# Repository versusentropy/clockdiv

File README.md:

# eurorack clockdivider

## v0.3 this version is not yet tested!

## Classic CD4024 7 step binary clock-divider

  * 6hp
  * +/-12V 20mA/-
  * 1 PCB 2 layer
    * 73 parts total
    * 14 SMT, 4 THT
  * +5V gate outputs
  * clock input
    * TN pin header on pcb
  * reset input
    * 2nd pin header on pcb

Schematic and layout with KiCad 5. Panel with Inkscape + shenzen2svg → Kicad

Ordered mine at JLCPCB. Gerbers include marking for order number. BOM with part numbers for their assembly service.

Be carful with the transisors' pin numbers, because the 2N3904 schematic symbol doesn't match the MMBT3904 part (, which has its own schematic symbol). 

The CLK input is buffered and inverted by Q2.

The RESET input (and the additional pin-header) are buffered by Q3 & Q4. Q1 resets the clockdivider at startup, until C1 is charged up.

A MMBT3904 buffers each output and its LED. The jack is protected by a diode and a 1k resistor. So multiple jacks can be combined.

On the back pin headers allow connections to other modules (not prtected by diodes, but a 1k resistor).

L78L06 to power everything else with 6.0V.

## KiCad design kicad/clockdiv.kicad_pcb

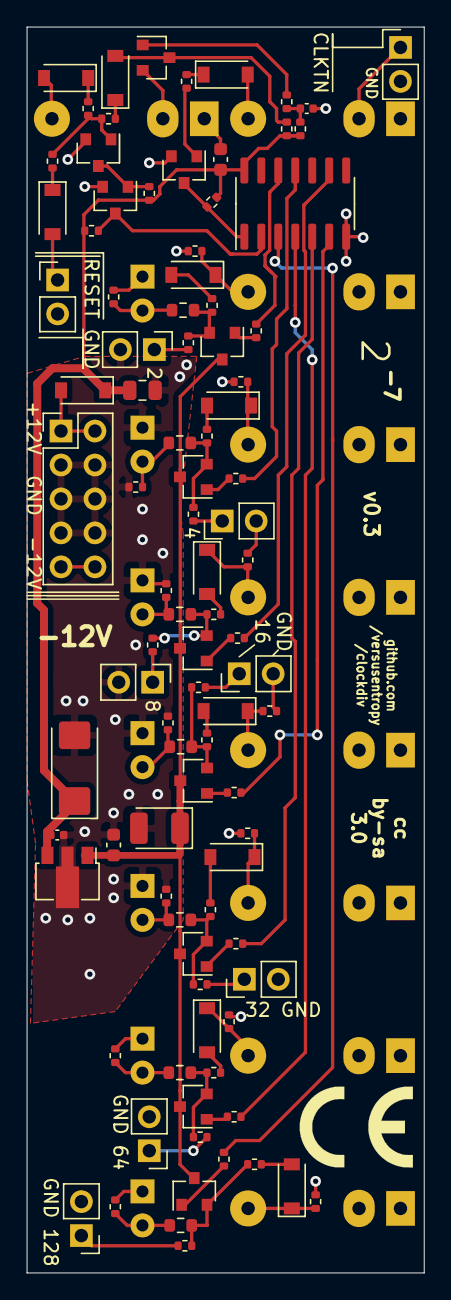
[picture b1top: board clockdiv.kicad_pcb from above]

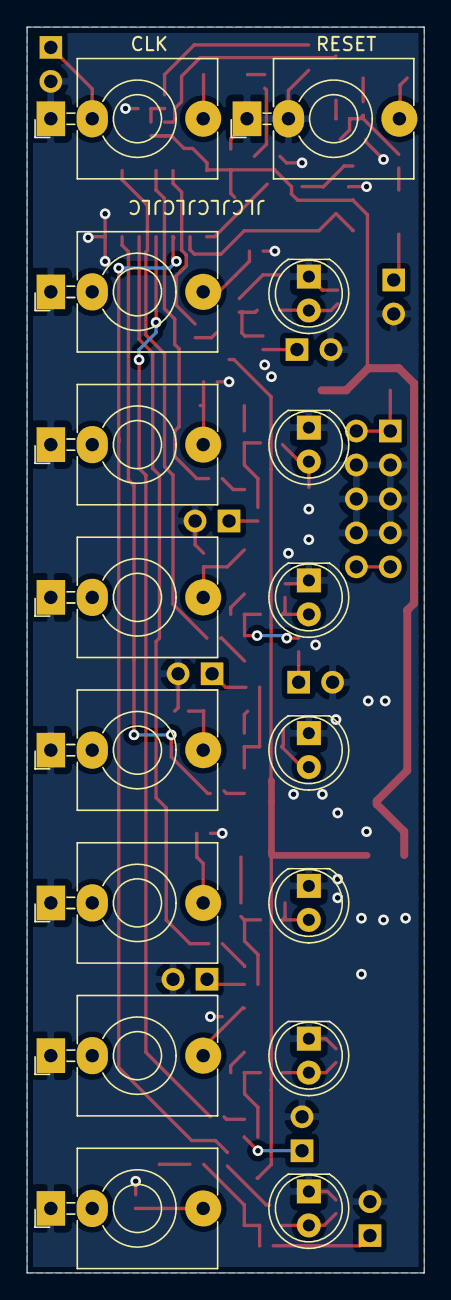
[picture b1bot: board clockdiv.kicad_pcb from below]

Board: 2 copper layers, 29.7 x 93.2 mm, 110 parts (16 on the bottom side), 70 nets.

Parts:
C1: 1u; C_0402_1005Metric
C2, C7: 100n; C_0603_1608Metric
C3: 330n; C_0402_1005Metric
C4: 22u; C_0805_2012Metric
C5: 10u; CP_EIA-6032-28_Kemet-C
C6: 22u; CP_EIA-3528-21_Kemet-B
D1, D2, D3, D4, D5, D13, D14, D15, D16, D17, D18, D19: 1N4148; D_SOD-123
D6, D7, D8, D9, D10, D11, D12: LED; LED_D5.0mm
J1: CLK; Jack_3.5mm_QingPu_WQP-PJ398SM_Vertical_CircularHolesSMALL
J2: RESET; Jack_3.5mm_QingPu_WQP-PJ398SM_Vertical_CircularHolesSMALL
J3: RESET GND; PinHeader_1x02_P2.54mm_Vertical
J4, J5, J6, J7, J8, J9, J12: OUT; Jack_3.5mm_QingPu_WQP-PJ398SM_Vertical_CircularHolesSMALL
J10: CLKTN GND; PinHeader_1x02_P2.54mm_Vertical
J11: +12V GND -12V; PinHeader_2x05_P2.54mm_Vertical
J13, J14, J15, J16, J17, J18, J19: GND; PinHeader_1x02_P2.54mm_Vertical
Q1, Q2, Q3, Q4, Q5, Q6, Q7, Q8, Q9, Q10, Q11: 2N3904; SOT-23
R1, R10, R13, R16, R19, R22, R25, R28: 100k; R_0402_1005Metric
R2, R3, R8, R9, R11: 10k; R_0402_1005Metric
R4, R5, R6, R7: 47k; R_0402_1005Metric
R12, R14, R17, R20, R23, R26, R29, R46, R47, R48, R49, R50, R51, R52: 1k; R_0402_1005Metric
R15, R18, R21, R24, R27, R30, R31: 470; R_0603_1608Metric
R32, R33, R34, R35, R36, R37, R38, R39, R40, R41, R42, R43, R44, R45: 1M; R_0402_1005Metric
U1: 4024; SOIC-14_3.9x8.7mm_P1.27mm
U2: L78L06_SOT89; SOT-89-3

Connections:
+6V: C6.1, C7.2, Q5.3, Q6.3, Q7.3, Q8.3, Q9.3, Q10.3, Q11.3, U2.1
+12V: C2.2, C3.2, C4.1, C5.1, D5.1, R1.2, R3.1, R8.1, R9.1, R11.1, U1.14, U2.3
/divider/CLOCK_INV: Q2.3, R8.2, U1.1
/divider/OUT1: R13.1, U1.12
/divider/OUT2: R19.1, U1.11
/divider/OUT3: R16.1, U1.9
/divider/OUT4: R22.1, U1.6
/divider/OUT5: R25.1, U1.5
/divider/OUT6: R28.1, U1.4
/divider/OUT7: R10.1, U1.3
/divider/RESET: Q4.3, R11.2, U1.2
GNDREF: C1.2, C2.1, C3.1, C4.2, C5.2, C6.2, C7.1, D6.1, D7.1, D8.1, D9.1, D10.1, D11.1, D12.1, J1.S, J2.S, J2.TN, J3.2, J4.S, J5.S, J6.S, J7.S, J8.S, J9.S, J10.2, J11.3, J11.4, J11.5, J11.6, J11.7, J11.8, J12.S, J13.2, J14.2, J15.2, J16.2, J17.2, J18.2, J19.2, Q1.2, Q2.2, Q3.2, Q4.2, R32.2, R33.1, R34.2, R35.1, R36.2, R37.1, R38.2, R39.1, R40.2, R41.1, R42.2, R43.1, R44.2, R45.1, U1.7, U2.2
unnamed: C1.1, R1.1, R2.2
unnamed: D1.1, R4.1
unnamed: D1.2, J1.T
unnamed: D2.1, R5.1
unnamed: D2.2, J2.T
unnamed: D3.1, R6.1
unnamed: D3.2, J3.1
unnamed: D4.1, R7.1
unnamed: D4.2, Q1.3, R3.2
unnamed: D5.2, J11.1, J11.2
unnamed: D6.2, R31.2, R45.2
unnamed: D7.2, R15.2, R33.2
unnamed: D8.2, R18.2, R35.2
unnamed: D9.2, R21.2, R37.2
unnamed: D10.2, R24.2, R39.2
unnamed: D11.2, R27.2, R41.2
unnamed: D12.2, R30.2, R43.2
unnamed: D13.1, J4.T, R32.1
unnamed: D13.2, R14.2
unnamed: D14.1, J5.T, R34.1
unnamed: D14.2, R17.2
unnamed: D15.1, J6.T, R36.1
unnamed: D15.2, R20.2
unnamed: D16.1, J7.T, R38.1
unnamed: D16.2, R23.2
unnamed: D17.1, J8.T, R40.1
unnamed: D17.2, R26.2
unnamed: D18.1, J9.T, R42.1
unnamed: D18.2, R29.2
unnamed: D19.1, J12.T, R44.1
unnamed: D19.2, R12.2
unnamed: J1.TN, J10.1
unnamed: J11.9, J11.10
unnamed: J13.1, R46.2
unnamed: J14.1, R47.2
unnamed: J15.1, R48.2
unnamed: J16.1, R49.2
unnamed: J17.1, R50.2
unnamed: J18.1, R51.2
unnamed: J19.1, R52.2
unnamed: Q1.1, R2.1
unnamed: Q2.1, R4.2
unnamed: Q3.1, R5.2, R6.2, R7.2
unnamed: Q3.3, Q4.1, R9.2
unnamed: Q5.1, R10.2
unnamed: Q5.2, R12.1, R31.1, R52.1
unnamed: Q6.1, R13.2
unnamed: Q6.2, R14.1, R15.1, R46.1
unnamed: Q7.1, R16.2
unnamed: Q7.2, R17.1, R18.1, R47.1
unnamed: Q8.1, R19.2
unnamed: Q8.2, R20.1, R21.1, R48.1
unnamed: Q9.1, R22.2
unnamed: Q9.2, R23.1, R24.1, R49.1
unnamed: Q10.1, R25.2
unnamed: Q10.2, R26.1, R27.1, R50.1
unnamed: Q11.1, R28.2
unnamed: Q11.2, R29.1, R30.1, R51.1

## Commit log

2021-11-05 init
2021-11-05 cut SVGs
2021-11-05 better pics
2021-11-05 resisze pcb
2021-11-05 remove git trash
2021-11-05 fix part count
2021-11-25 Use 6V. Add output diodes + output pin headers
2021-11-25 README
2021-11-25 gerbers for v0.3 + BOM+POS + doc
2021-11-25 layout pic
